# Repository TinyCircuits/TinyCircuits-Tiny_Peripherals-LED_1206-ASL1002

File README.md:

# TinyCircuits Tiny Peripheral 1206 LED
# ASL1002 Rev3

The design files are located under design_files/ for the TinyCircuits ASL1002 Rev 3 PCB.  This is a Tiny peripheral board that has an 1206 LED and resistor, along with pads to solder to.

Format is in Cadsoft Eagle format - Eagle version 6.2 was used for the original design.

For more infomation on this, check out the product page at TinyCircuits.com: 
https://tinycircuits.com/collections/tinylily/products/tinylily-led-1206

# License:

Design by TinyCircuits.
All design files are released under the Creative Commons Attribution Share-Alike 3.0 License, see the following link for details: http://creativecommons.org/licenses/by-sa/3.0

All text above must be included in any redistribution or derived design

This project uses designs and concepts developed as part of the Arduino project and the LilyPad project.  The TinyCircuits design files themselves (schematics, PCB and libraries) are not directly derived from these works' design files and have been created new, however the concepts and basic architecture behind the TinyDuino and TinyLily products are derived and we thank the hard work of the organizations below for their contributions to open-source hardware:
  
Original Arduino Uno Design by Team Arduino

LilyPad Arduino Design by Leah Buechley and Sparkfun Electronics

Please support the open-source hardware community

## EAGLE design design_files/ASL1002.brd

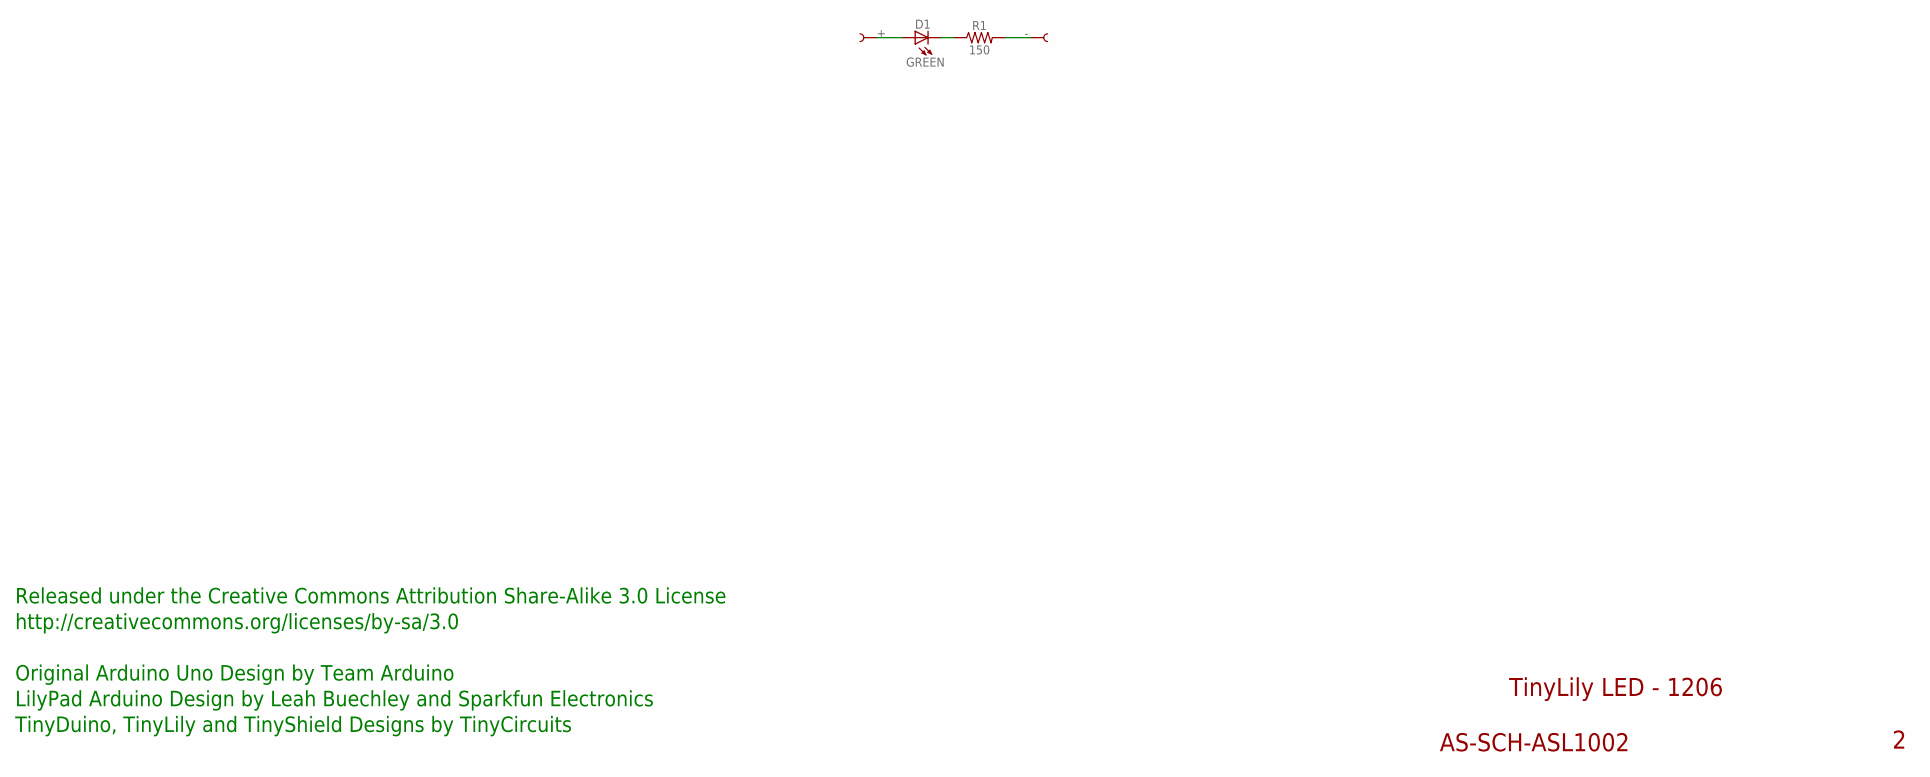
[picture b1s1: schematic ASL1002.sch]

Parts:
D1: GREEN; 1206_LED; PARTNO AS-ITM-00039
R1: 150; R0805
U$1, U$7: SEWTABTH_1206; SEWTAP_TH_1206

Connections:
+: D1.1 (A), U$7.1
-: R1.2, U$1.1
unnamed: D1.2 (C), R1.1

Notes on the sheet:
TinyLily LED - 1206
AS-SCH-ASL1002
Released under the Creative Commons Attribution Share-Alike 3.0 License
http://creativecommons.org/licenses/by-sa/3.0
Original Arduino Uno Design by Team Arduino
TinyDuino, TinyLily and TinyShield Designs by TinyCircuits
LilyPad Arduino Design by Leah Buechley and Sparkfun Electronics

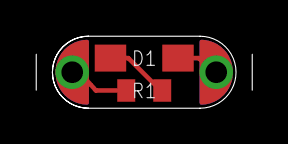
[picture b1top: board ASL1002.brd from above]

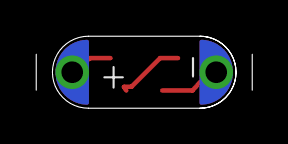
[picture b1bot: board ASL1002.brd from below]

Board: 2 copper layers, 12.0 x 4.0 mm, 5 parts (2 on the bottom side), 3 nets.

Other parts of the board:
U$6: DOCFIELD-TINYCIRCUITS-PCB

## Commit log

2013-06-30 Updated project link
2014-08-24 Updated Link
2016-02-02 Updated to Rev 2
2019-01-04 update format
2019-08-01 example code
2020-08-28 Add CAD data
